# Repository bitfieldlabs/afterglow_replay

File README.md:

# afterglow replay
The afterglow replay is a mini PCB which can run the attract mode of a Williams Tales of the Arabian Nights pinball machine. It is pure decorative and serves no real purpose :-)
See a video of the board in action:<br>

## Notes
### Power
The board can operate from 3.3V-5V directly.
### Atmega328P
The Atmega328P must be fused as follows: lfuse 0xff, hfuse 0xda, efuse 0xfd.

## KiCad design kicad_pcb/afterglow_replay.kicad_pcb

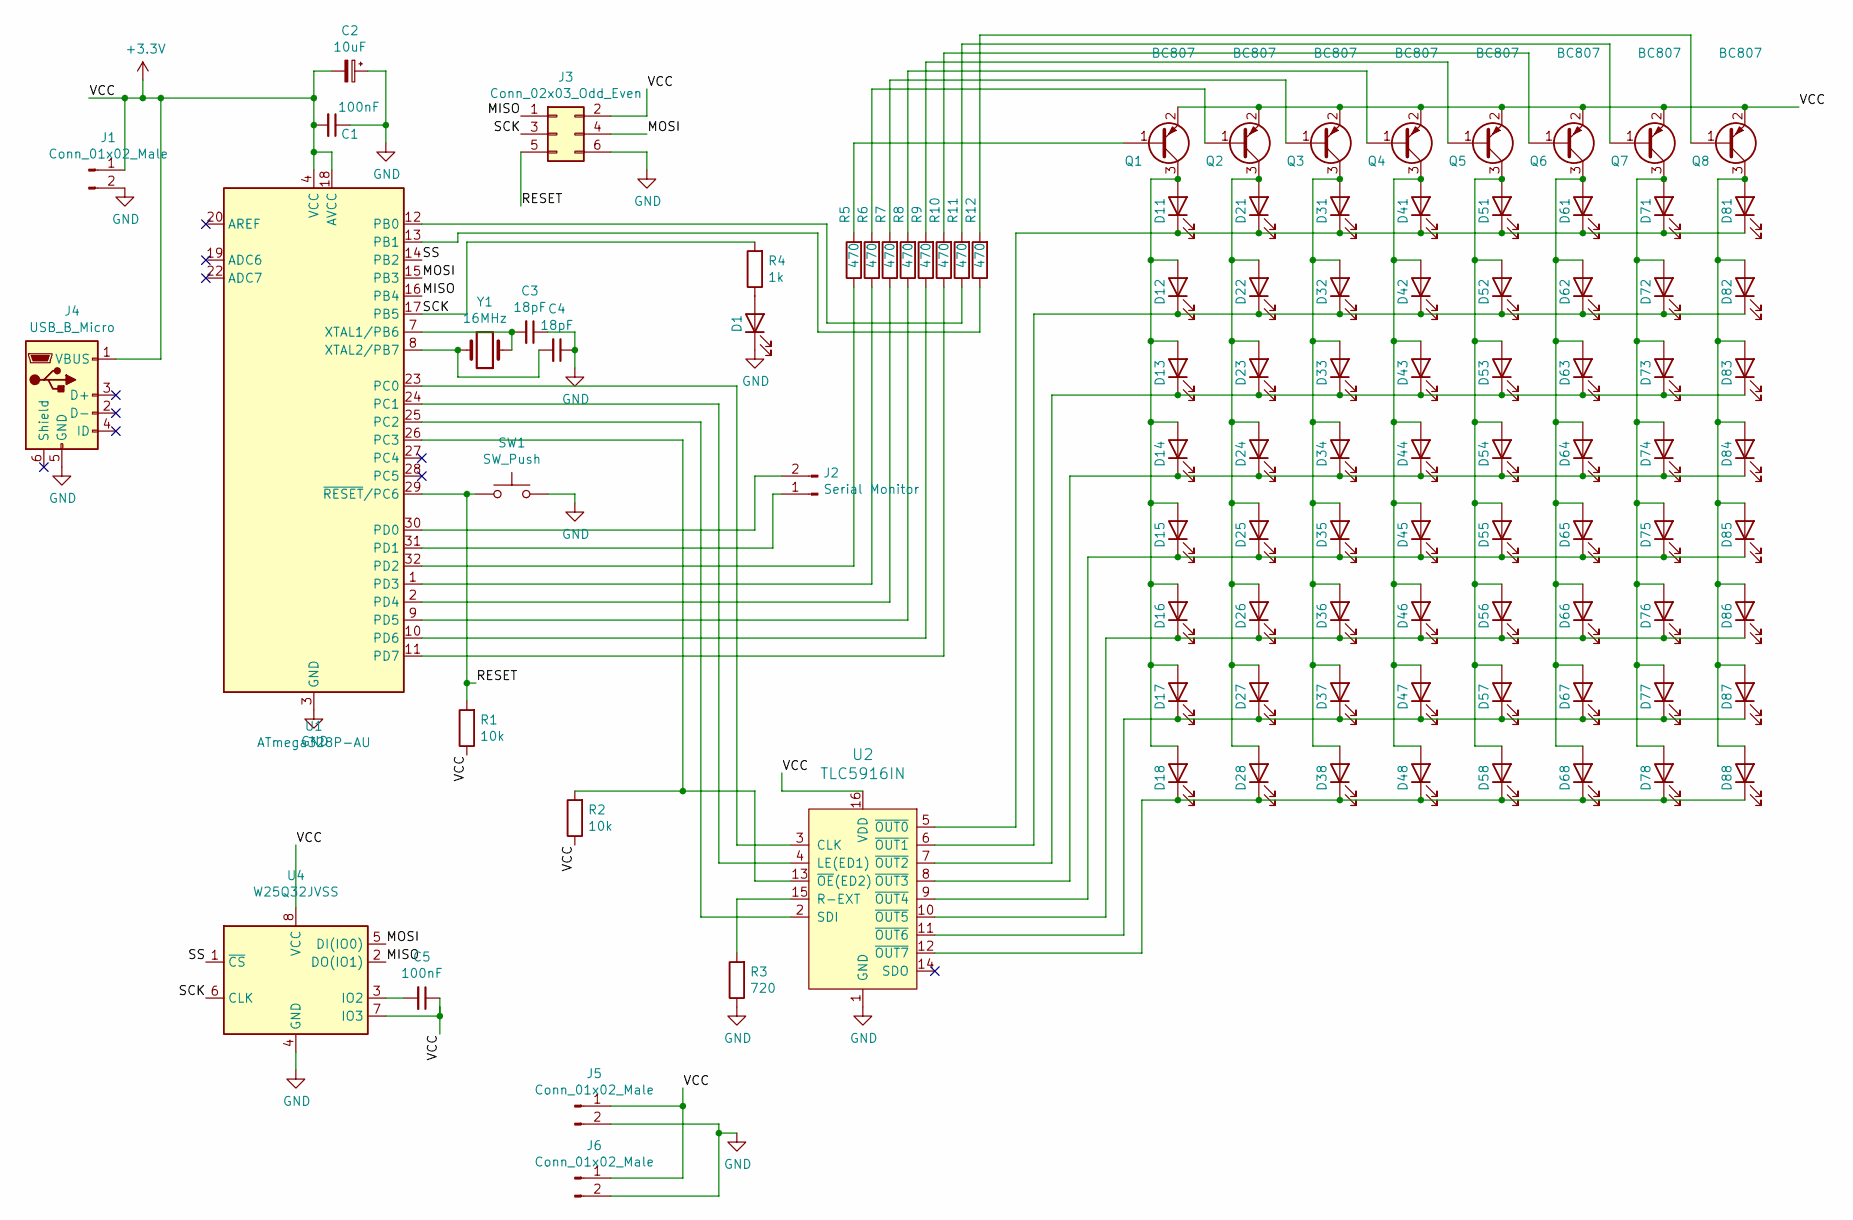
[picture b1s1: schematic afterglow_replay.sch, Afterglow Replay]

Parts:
C1, C5: 100nF; C_0805_HandSoldering
C2: 10uF; CP_Elec_4x5.3
C3, C4: 18pF; C_0805_HandSoldering
D1, D11, D12, D13, D14, D15, D16, D17, D18, D21, D22, D23, D24, D25, D26, D27, D28, D31, D32, D33, D34, D35, D36, D37, D38, D41, D42, D43, D44, D45, D46, D47, D48, D51, D52, D53, D54, D55, D56, D57, D58, D61, D62, D63, D64, D65, D66, D67, D68, D71, D72, D73, D74, D75, D76, D77, D78, D81, D82, D83, D84, D85, D86, D87, D88: LED; LED_0805_HandSoldering
J1, J5, J6: Conn_01x02_Male; Pin_Header_Straight_1x02_Pitch2.54mm
J2: Serial Monitor; Pin_Header_Straight_1x02_Pitch2.54mm
J3: Conn_02x03_Odd_Even; Pin_Header_Straight_2x03_Pitch2.54mm
J4: USB_B_Micro; USB_Micro-B_Molex-105017-0001
Q1, Q2, Q3, Q4, Q5, Q6, Q7, Q8: BC807; SOT-23_Handsoldering
R1, R2: 10k; R_0805_HandSoldering
R3: 720; R_0805_HandSoldering
R4: 1k; R_0805_HandSoldering
R5, R6, R7, R8, R9, R10, R11, R12: 470; R_0805_HandSoldering
SW1: SW_Push; Panasonic_EVQPUK_EVQPUB
U1: ATmega328P-AU; TQFP-32_7x7mm_Pitch0.8mm
U2: TLC5916IN; SOIC-16_3.9x9.9mm_Pitch1.27mm; MPN TLC5916IN; Digi-Key_PN 296-24383-5-ND
U4: W25Q32JVSS; SOIJ-8_5.3x5.3mm_Pitch1.27mm
Y1: 16MHz; Crystal_SMD_0603-2pin_6.0x3.5mm_HandSoldering

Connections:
+3V3: C1.2, C2.2, C5.1, J1.1, J3.2, J4.1 (VBUS), J5.1, J6.1, Q1.2 (E), Q2.2 (E), Q3.2 (E), Q4.2 (E), Q5.2 (E), Q6.2 (E), Q7.2 (E), Q8.2 (E), R1.1, R2.1, U1.4 (VCC), U1.6 (VCC), U1.18 (AVCC), U2.16 (VDD), U4.7 (IO3), U4.8 (VCC)
/MISO: J3.1, U1.16 (PB4), U4.2 (DO(IO1))
/MOSI: J3.4, U1.15 (PB3), U4.5 (DI(IO0))
/RESET: J3.5, R1.2, SW1.1, U1.29 (~RESET~/PC6)
/SCK: J3.3, R4.2, U1.17 (PB5), U4.6 (CLK)
/SS: U1.14 (PB2), U4.1 (~CS)
GND: C1.1, C2.1, C3.1, C4.1, D1.1 (K), J1.2, J3.6, J4.5 (GND), J5.2, J6.2, R3.1, SW1.2, U1.3 (GND), U1.5 (GND), U1.21 (GND), U2.1 (GND), U4.4 (GND)
unnamed: C3.2, U1.7 (XTAL1/PB6), Y1.1
unnamed: C4.2, U1.8 (XTAL2/PB7), Y1.2
unnamed: C5.2, U4.3 (IO2)
unnamed: D1.2 (A), R4.1
unnamed: D11.1 (K), D21.1 (K), D31.1 (K), D41.1 (K), D51.1 (K), D61.1 (K), D71.1 (K), D81.1 (K), U2.5 (~OUT0)
unnamed: D11.2 (A), D12.2 (A), D13.2 (A), D14.2 (A), D15.2 (A), D16.2 (A), D17.2 (A), D18.2 (A), Q1.3 (C)
unnamed: D12.1 (K), D22.1 (K), D32.1 (K), D42.1 (K), D52.1 (K), D62.1 (K), D72.1 (K), D82.1 (K), U2.6 (~OUT1)
unnamed: D13.1 (K), D23.1 (K), D33.1 (K), D43.1 (K), D53.1 (K), D63.1 (K), D73.1 (K), D83.1 (K), U2.7 (~OUT2)
unnamed: D14.1 (K), D24.1 (K), D34.1 (K), D44.1 (K), D54.1 (K), D64.1 (K), D74.1 (K), D84.1 (K), U2.8 (~OUT3)
unnamed: D15.1 (K), D25.1 (K), D35.1 (K), D45.1 (K), D55.1 (K), D65.1 (K), D75.1 (K), D85.1 (K), U2.9 (~OUT4)
unnamed: D16.1 (K), D26.1 (K), D36.1 (K), D46.1 (K), D56.1 (K), D66.1 (K), D76.1 (K), D86.1 (K), U2.10 (~OUT5)
unnamed: D17.1 (K), D27.1 (K), D37.1 (K), D47.1 (K), D57.1 (K), D67.1 (K), D77.1 (K), D87.1 (K), U2.11 (~OUT6)
unnamed: D18.1 (K), D28.1 (K), D38.1 (K), D48.1 (K), D58.1 (K), D68.1 (K), D78.1 (K), D88.1 (K), U2.12 (~OUT7)
unnamed: D21.2 (A), D22.2 (A), D23.2 (A), D24.2 (A), D25.2 (A), D26.2 (A), D27.2 (A), D28.2 (A), Q2.3 (C)
unnamed: D31.2 (A), D32.2 (A), D33.2 (A), D34.2 (A), D35.2 (A), D36.2 (A), D37.2 (A), D38.2 (A), Q3.3 (C)
unnamed: D41.2 (A), D42.2 (A), D43.2 (A), D44.2 (A), D45.2 (A), D46.2 (A), D47.2 (A), D48.2 (A), Q4.3 (C)
unnamed: D51.2 (A), D52.2 (A), D53.2 (A), D54.2 (A), D55.2 (A), D56.2 (A), D57.2 (A), D58.2 (A), Q5.3 (C)
unnamed: D61.2 (A), D62.2 (A), D63.2 (A), D64.2 (A), D65.2 (A), D66.2 (A), D67.2 (A), D68.2 (A), Q6.3 (C)
unnamed: D71.2 (A), D72.2 (A), D73.2 (A), D74.2 (A), D75.2 (A), D76.2 (A), D77.2 (A), D78.2 (A), Q7.3 (C)
unnamed: D81.2 (A), D82.2 (A), D83.2 (A), D84.2 (A), D85.2 (A), D86.2 (A), D87.2 (A), D88.2 (A), Q8.3 (C)
unnamed: J2.1, U1.31 (PD1)
unnamed: J2.2, U1.30 (PD0)
unnamed: Q1.1 (B), R5.2
unnamed: Q2.1 (B), R6.2
unnamed: Q3.1 (B), R7.2
unnamed: Q4.1 (B), R8.2
unnamed: Q5.1 (B), R9.2
unnamed: Q6.1 (B), R10.2
unnamed: Q7.1 (B), R11.2
unnamed: Q8.1 (B), R12.2
unnamed: R2.2, U1.26 (PC3), U2.13 (~OE~(ED2))
unnamed: R3.2, U2.15 (R-EXT)
unnamed: R5.1, U1.32 (PD2)
unnamed: R6.1, U1.1 (PD3)
unnamed: R7.1, U1.2 (PD4)
unnamed: R8.1, U1.9 (PD5)
unnamed: R9.1, U1.10 (PD6)
unnamed: R10.1, U1.11 (PD7)
unnamed: R11.1, U1.12 (PB0)
unnamed: R12.1, U1.13 (PB1)
unnamed: U1.23 (PC0), U2.3 (CLK)
unnamed: U1.24 (PC1), U2.4 (LE(ED1))
unnamed: U1.25 (PC2), U2.2 (SDI)

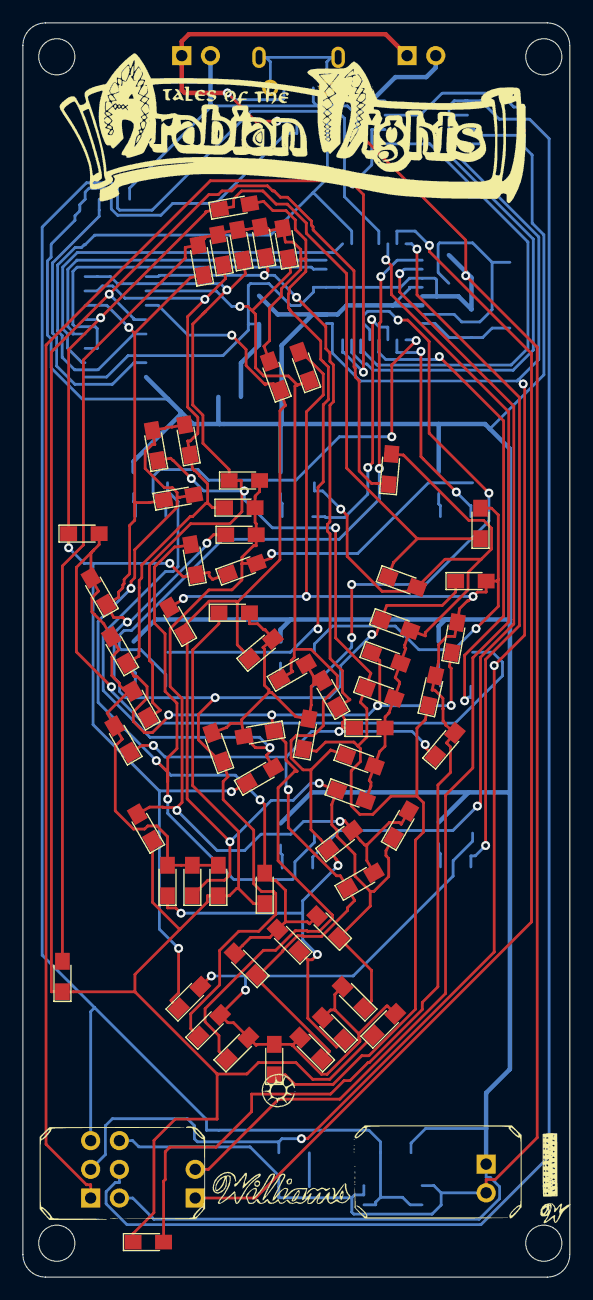
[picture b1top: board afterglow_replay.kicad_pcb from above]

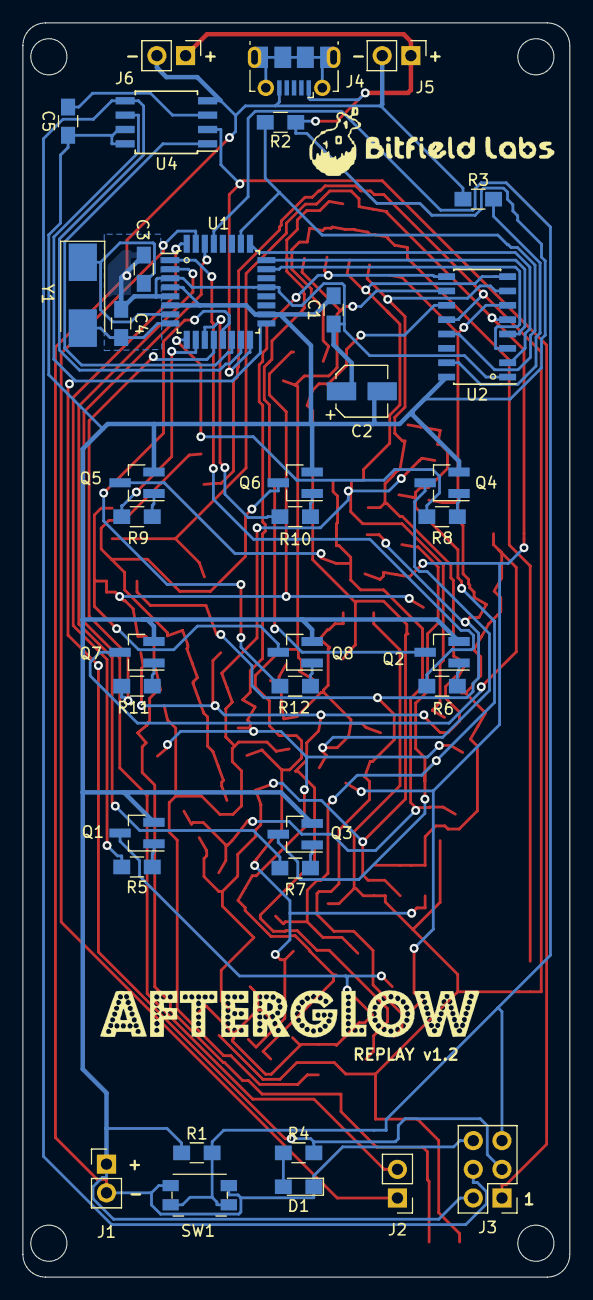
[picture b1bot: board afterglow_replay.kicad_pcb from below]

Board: 2 copper layers, 48.4 x 111.0 mm, 105 parts (37 on the bottom side), 50 nets.

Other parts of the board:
OL: MountingHole_3.2mm_M3_DIN965
OR: MountingHole_3.2mm_M3_DIN965
PLAYFIELD: LOGO; totan
UL: MountingHole_3.2mm_M3_DIN965

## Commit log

2020-12-19 Tidying up
2020-12-20 Squeezing in a few more replay bytes
2020-12-20 Schematic v1.1 fixes the most stupid errors
2020-12-30 PCB v1.1
2021-02-07 PCB v1.2
2021-02-07 PCB v1.2 slightly less wide
2021-02-10 Added a kicad project archive
